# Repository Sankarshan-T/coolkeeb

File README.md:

# coolkeeb (driftpad)
A cool little keyboard with 5 keys i made to play Asphalt without using the whole keyboard. A pretty simple project in terms of complexity, but i spen a lot of time and effort building this. One of my first ever proper hardware projects :D

## Features
- Completely 3D printed casing
- 5 key switches
- Uses QMK firmware
- Customizable case and colors

## About the case
The top plate snaps into the container perfectly with exact tolerence. It has 3 parts: the top plate, the container, and the angle supporter (supposed to be glued on). Aditionally, i added some decorations like thunderolts that can be fitted onto the top plate as well! I went with blue and white for the case this time, as i thought it looked cool!

## The PCB
Here are the images of the PCB and the schematic. Very simple as i do not know much in this field of work :D

## Firmware Overview
This hackpad uses QMK firmware.

- The 5 keys currently act as macros I dynamically change in my code.

Thats all for now, i may add other stuff now, this is just the basic version

## BOM
This is all you need to make this yourself, nothing too much :D
- 5x Cherry MX Switches
- 5x DSA Keycaps (I 3d printed these mysef tho)
- 1x XIAO RP2040
- 1x Case (3 printed parts)
- 1x PCB

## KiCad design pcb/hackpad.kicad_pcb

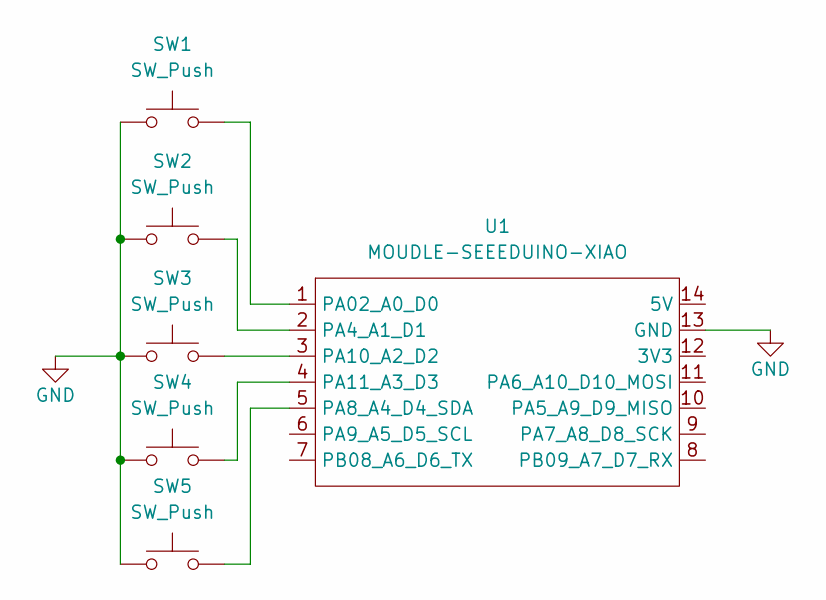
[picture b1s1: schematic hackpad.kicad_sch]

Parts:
SW1, SW2, SW3, SW4, SW5: SW_Push; SW_Cherry_MX_1.00u_PCB
U1: MOUDLE-SEEEDUINO-XIAO; XIAO-Generic-Hybrid-14P-2.54-21X17.8MM

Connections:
GND: SW1.1, SW2.1, SW3.1, SW4.1, SW5.1, U1.13 (GND)
unnamed: SW1.2, U1.1 (PA02_A0_D0)
unnamed: SW2.2, U1.2 (PA4_A1_D1)
unnamed: SW5.2, U1.5 (PA8_A4_D4_SDA)
unnamed: SW3.2, U1.3 (PA10_A2_D2)
unnamed: SW4.2, U1.4 (PA11_A3_D3)

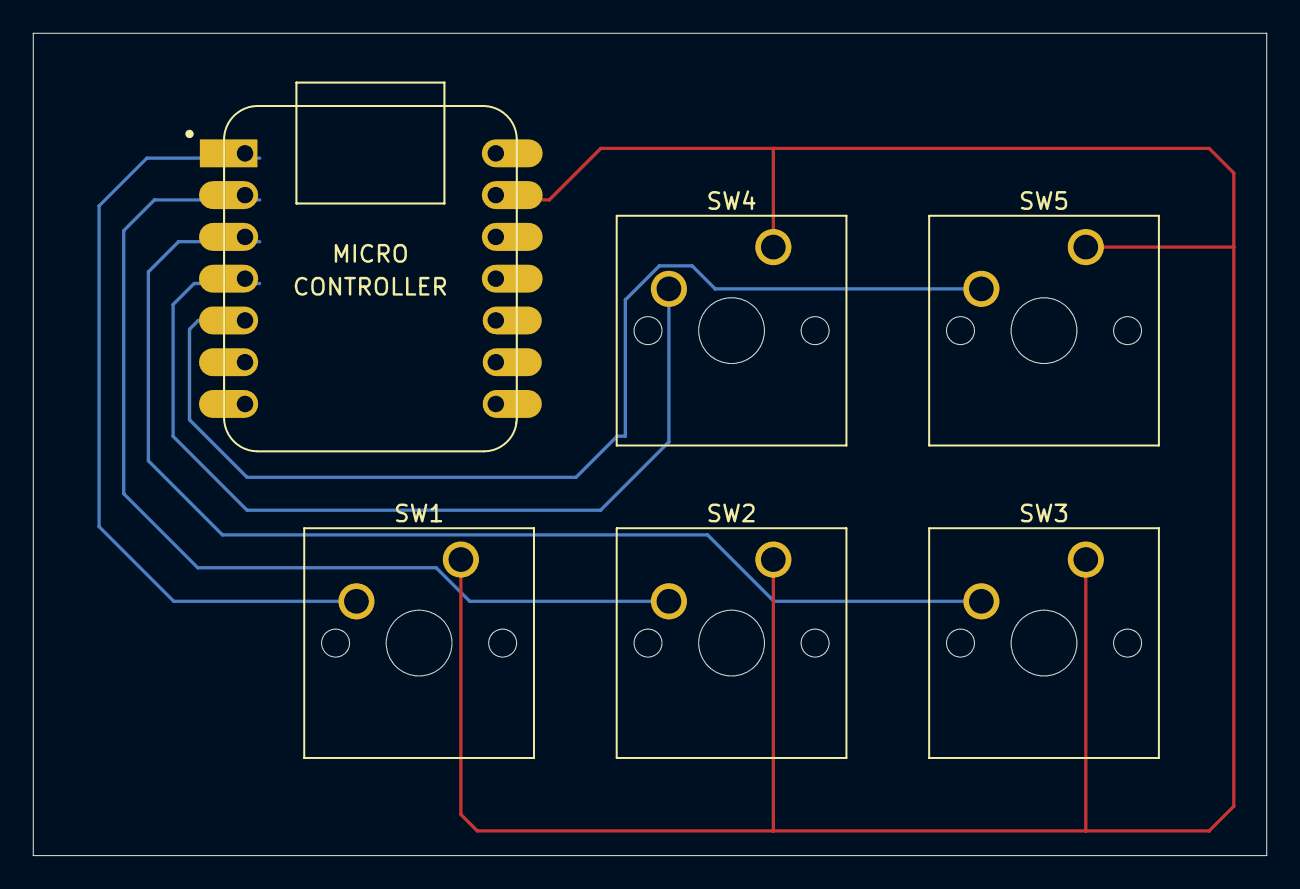
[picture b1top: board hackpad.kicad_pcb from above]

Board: 2 copper layers, 75.0 x 50.0 mm, 6 parts (0 on the bottom side), 6 nets.
